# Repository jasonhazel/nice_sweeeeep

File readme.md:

# nice!sweeeeep

A quick modification of [Sadek Baroudi's Sweeeeep](https://github.com/sadekbaroudi/sweeeeep) to use a nice!nano instead of Elite-C.

## CURRENTLY UNTESTED

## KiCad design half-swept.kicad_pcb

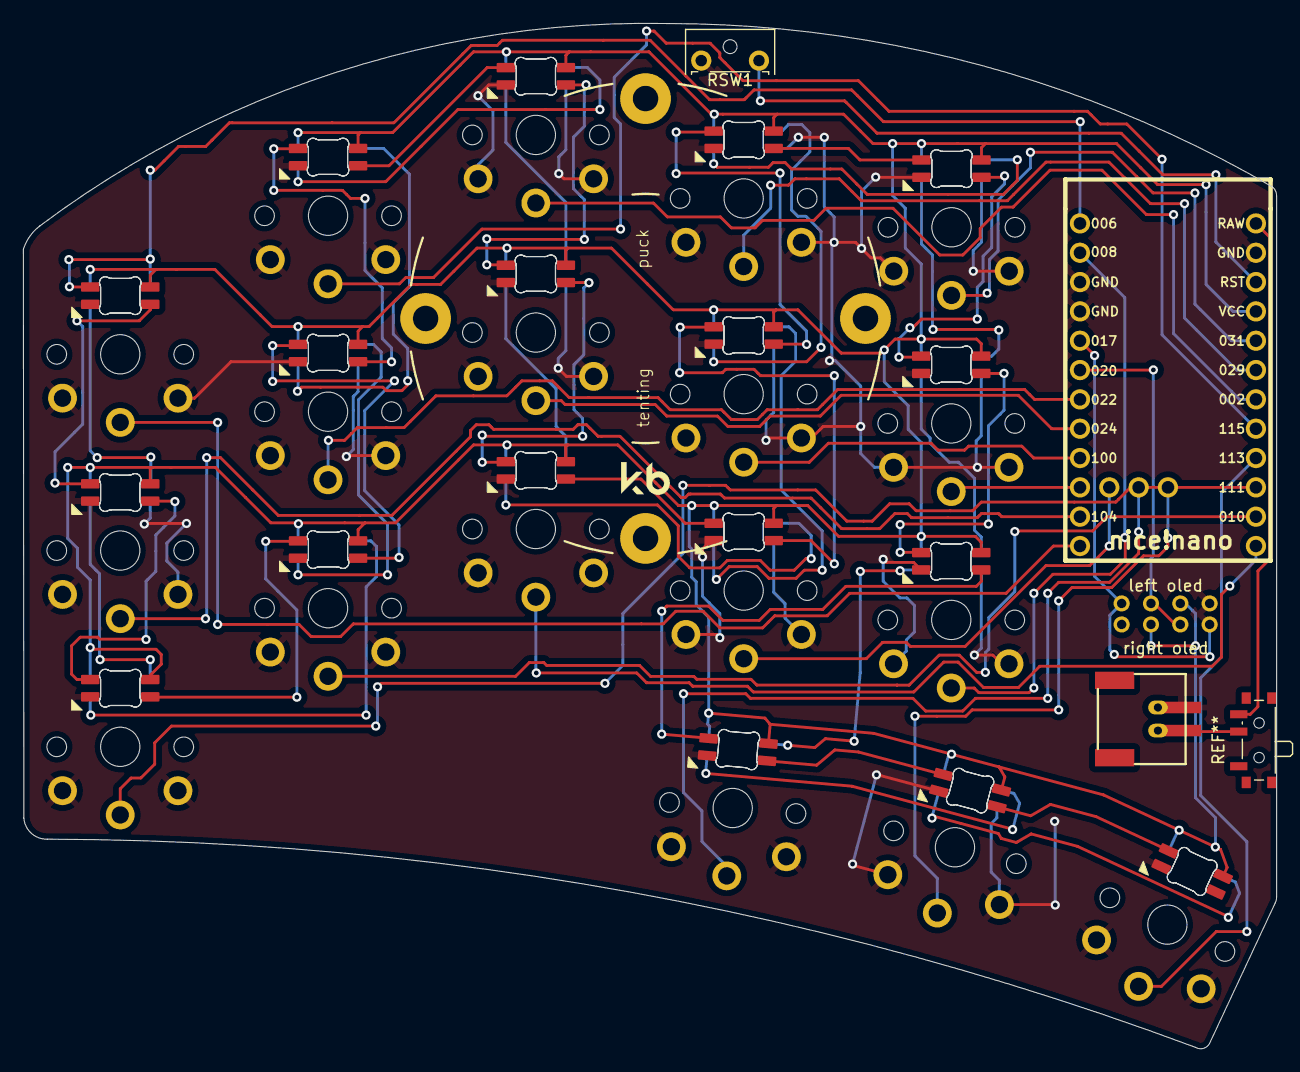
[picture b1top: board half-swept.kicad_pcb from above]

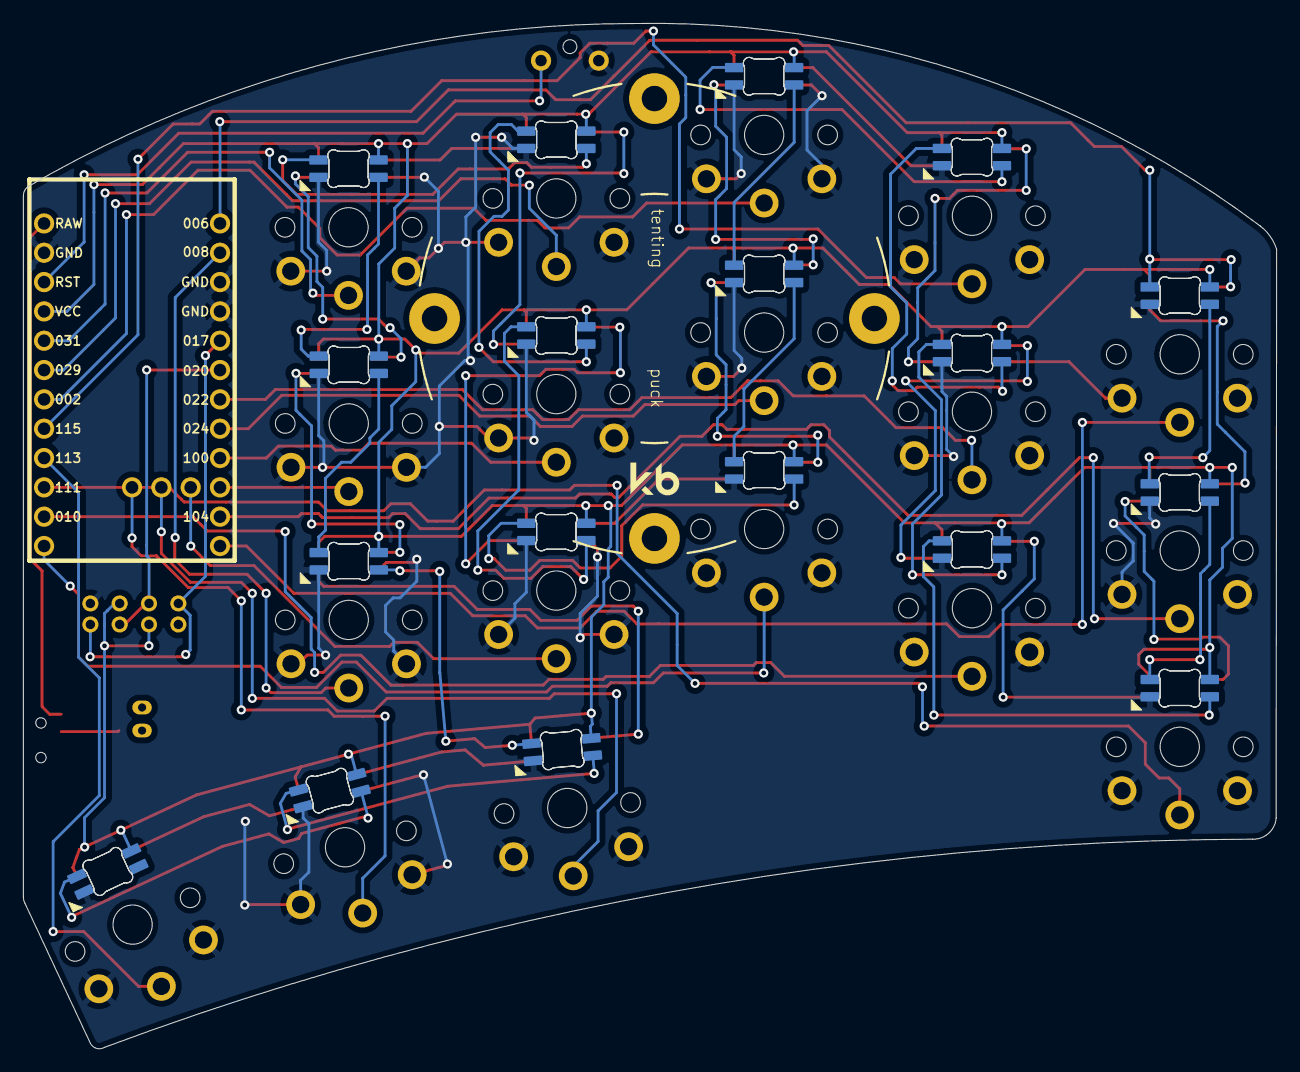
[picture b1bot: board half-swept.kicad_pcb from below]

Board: 2 copper layers, 108.6 x 88.8 mm, 59 parts (18 on the bottom side), 58 nets.

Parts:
D1, D2, D3, D4, D5, D6, D7, D8, D9, D10, D11, D12, D13, D14, D15, D16, D17, D18, D19, D20, D21, D22, D23, D24, D25, D26, D27, D28, D29, D30, D31, D32, D33, D34, D35, D36: SK6812MINI-E; MX_SK6812MINI-E_REV
JST_PH2_SMT: VAL**; JST_PH2_SMT_TH
OL1, OL2: OLED; OLED_v2
RSW1: SW_Push; SW_Tactile_SPST_Angled_MJTP1117-no-mount
SW1, SW2, SW3, SW4, SW5, SW6, SW8, SW9, SW10, SW11, SW12, SW14, SW15, SW16, SW17, SW18, SW20, SW21: SW_Push; Kailh-PG1350-1u-reversible
U2: nice_nano

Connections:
unnamed: D1.2 (DOUT), D4.4 (DIN)
unnamed: D2.2 (DOUT), D5.4 (DIN)
unnamed: D3.2 (DOUT), D6.4 (DIN)
unnamed: D4.2 (DOUT), D7.4 (DIN)
unnamed: D5.2 (DOUT), D8.4 (DIN)
unnamed: D6.2 (DOUT), D9.4 (DIN)
unnamed: D10.2 (DOUT), D13.4 (DIN)
unnamed: D7.2 (DOUT), D10.4 (DIN)
unnamed: D11.2 (DOUT), D14.4 (DIN)
unnamed: D8.2 (DOUT), D11.4 (DIN)
unnamed: D12.2 (DOUT), D15.4 (DIN)
unnamed: D9.2 (DOUT), D12.4 (DIN)
unnamed: D13.2 (DOUT), D16.4 (DIN)
unnamed: D14.2 (DOUT), D17.4 (DIN)
unnamed: D15.2 (DOUT), D18.4 (DIN)
unnamed: D2.4 (DIN), D16.2 (DOUT)
unnamed: D3.4 (DIN), D17.2 (DOUT)
unnamed: D19.2 (DOUT), D22.4 (DIN)
unnamed: D20.2 (DOUT), D23.4 (DIN)
unnamed: D20.4 (DIN), D34.2 (DOUT)
unnamed: D21.2 (DOUT), D24.4 (DIN)
unnamed: D21.4 (DIN), D35.2 (DOUT)
unnamed: D22.2 (DOUT), D25.4 (DIN)
unnamed: D23.2 (DOUT), D26.4 (DIN)
unnamed: D24.2 (DOUT), D27.4 (DIN)
unnamed: D25.2 (DOUT), D28.4 (DIN)
unnamed: D26.2 (DOUT), D29.4 (DIN)
unnamed: D27.2 (DOUT), D30.4 (DIN)
unnamed: D28.2 (DOUT), D31.4 (DIN)
unnamed: D29.2 (DOUT), D32.4 (DIN)
unnamed: D30.2 (DOUT), D33.4 (DIN)
unnamed: D31.2 (DOUT), D34.4 (DIN)
unnamed: D32.2 (DOUT), D35.4 (DIN)
unnamed: D33.2 (DOUT), D36.4 (DIN)
Switch1: SW2.1, U2.12 (9/PB5)
Switch2: SW3.1, U2.17 (A0/PF7)
Switch3: SW4.1, U2.18 (A1/PF6)
Switch4: SW5.1, U2.19 (A2/PF5)
Switch5: SW6.1, U2.20 (A3/PF4)
Switch6: SW8.1, U2.11 (8/PB4)
Switch7: SW9.1, U2.7 (4/PD4)
Switch8: SW10.1, U2.8 (5/PC6)
Switch9: SW11.1, U2.9 (6/PD7)
Switch10: SW12.1, U2.10 (7/PE6)
Switch11: SW14.1, U2.15 (14/PB3)
Switch12: SW15.1, U2.14 (16/PB2)
Switch13: SW16.1, U2.13 (10/PB6)
Switch14: SW17.1, U2.31
Switch15: SW18.1, U2.2 (RX1/PD2)
Switch16: SW20.1, U2.16 (15/PB1)
Switch17: SW21.1, U2.33
Switch18: SW1.1, U2.32
gnd: D1.3 (VSS), D2.3 (VSS), D3.3 (VSS), D4.3 (VSS), D5.3 (VSS), D6.3 (VSS), D7.3 (VSS), D8.3 (VSS), D9.3 (VSS), D10.3 (VSS), D11.3 (VSS), D12.3 (VSS), D13.3 (VSS), D14.3 (VSS), D15.3 (VSS), D16.3 (VSS), D17.3 (VSS), D18.3 (VSS), D19.3 (VSS), D20.3 (VSS), D21.3 (VSS), D22.3 (VSS), D23.3 (VSS), D24.3 (VSS), D25.3 (VSS), D26.3 (VSS), D27.3 (VSS), D28.3 (VSS), D29.3 (VSS), D30.3 (VSS), D31.3 (VSS), D32.3 (VSS), D33.3 (VSS), D34.3 (VSS), D35.3 (VSS), D36.3 (VSS), JST_PH2_SMT.1, OL1.4 (GND), OL2.4 (GND), RSW1.1, SW1.2, SW2.2, SW3.2, SW4.2, SW5.2, SW6.2, SW8.2, SW9.2, SW10.2, SW11.2, SW12.2, SW14.2, SW15.2, SW16.2, SW17.2, SW18.2, SW20.2, SW21.2, U2.3 (GND), U2.4 (GND), U2.23 (GND)
led: D1.4 (DIN), D19.4 (DIN), U2.1 (TX0/PD3)
reset: RSW1.2, U2.22 (RST)
scl: OL1.2 (SCL), OL2.2 (SCL), U2.6 (3/PD0)
sda: OL1.1 (SDA), OL2.1 (SDA), U2.5 (2/PD1)
vcc: D1.1 (VDD), D2.1 (VDD), D3.1 (VDD), D4.1 (VDD), D5.1 (VDD), D6.1 (VDD), D7.1 (VDD), D8.1 (VDD), D9.1 (VDD), D10.1 (VDD), D11.1 (VDD), D12.1 (VDD), D13.1 (VDD), D14.1 (VDD), D15.1 (VDD), D16.1 (VDD), D17.1 (VDD), D18.1 (VDD), D19.1 (VDD), D20.1 (VDD), D21.1 (VDD), D22.1 (VDD), D23.1 (VDD), D24.1 (VDD), D25.1 (VDD), D26.1 (VDD), D27.1 (VDD), D28.1 (VDD), D29.1 (VDD), D30.1 (VDD), D31.1 (VDD), D32.1 (VDD), D33.1 (VDD), D34.1 (VDD), D35.1 (VDD), D36.1 (VDD), OL1.3 (VCC), OL2.3 (VCC), U2.21 (VCC)

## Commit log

2022-10-21 init
2022-10-21 fix switch11 trace running through everyone's yard
